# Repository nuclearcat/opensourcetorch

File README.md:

Opensource programmable... torch? light? flashlight? I dont know, but it is funny and i like it.

We have onboard:
3xRGB(parallel) light, indicator light, accelerometer, illumination sensor, USB-Serial (CH340) for debug, lithium battery charger.

Example applications: coming soon

Read ERRATA first, if you want to make your own!

ERRATA in v1.0   
* 32Khz oscillator on MCU not starting reliably. (Might be software issue.)

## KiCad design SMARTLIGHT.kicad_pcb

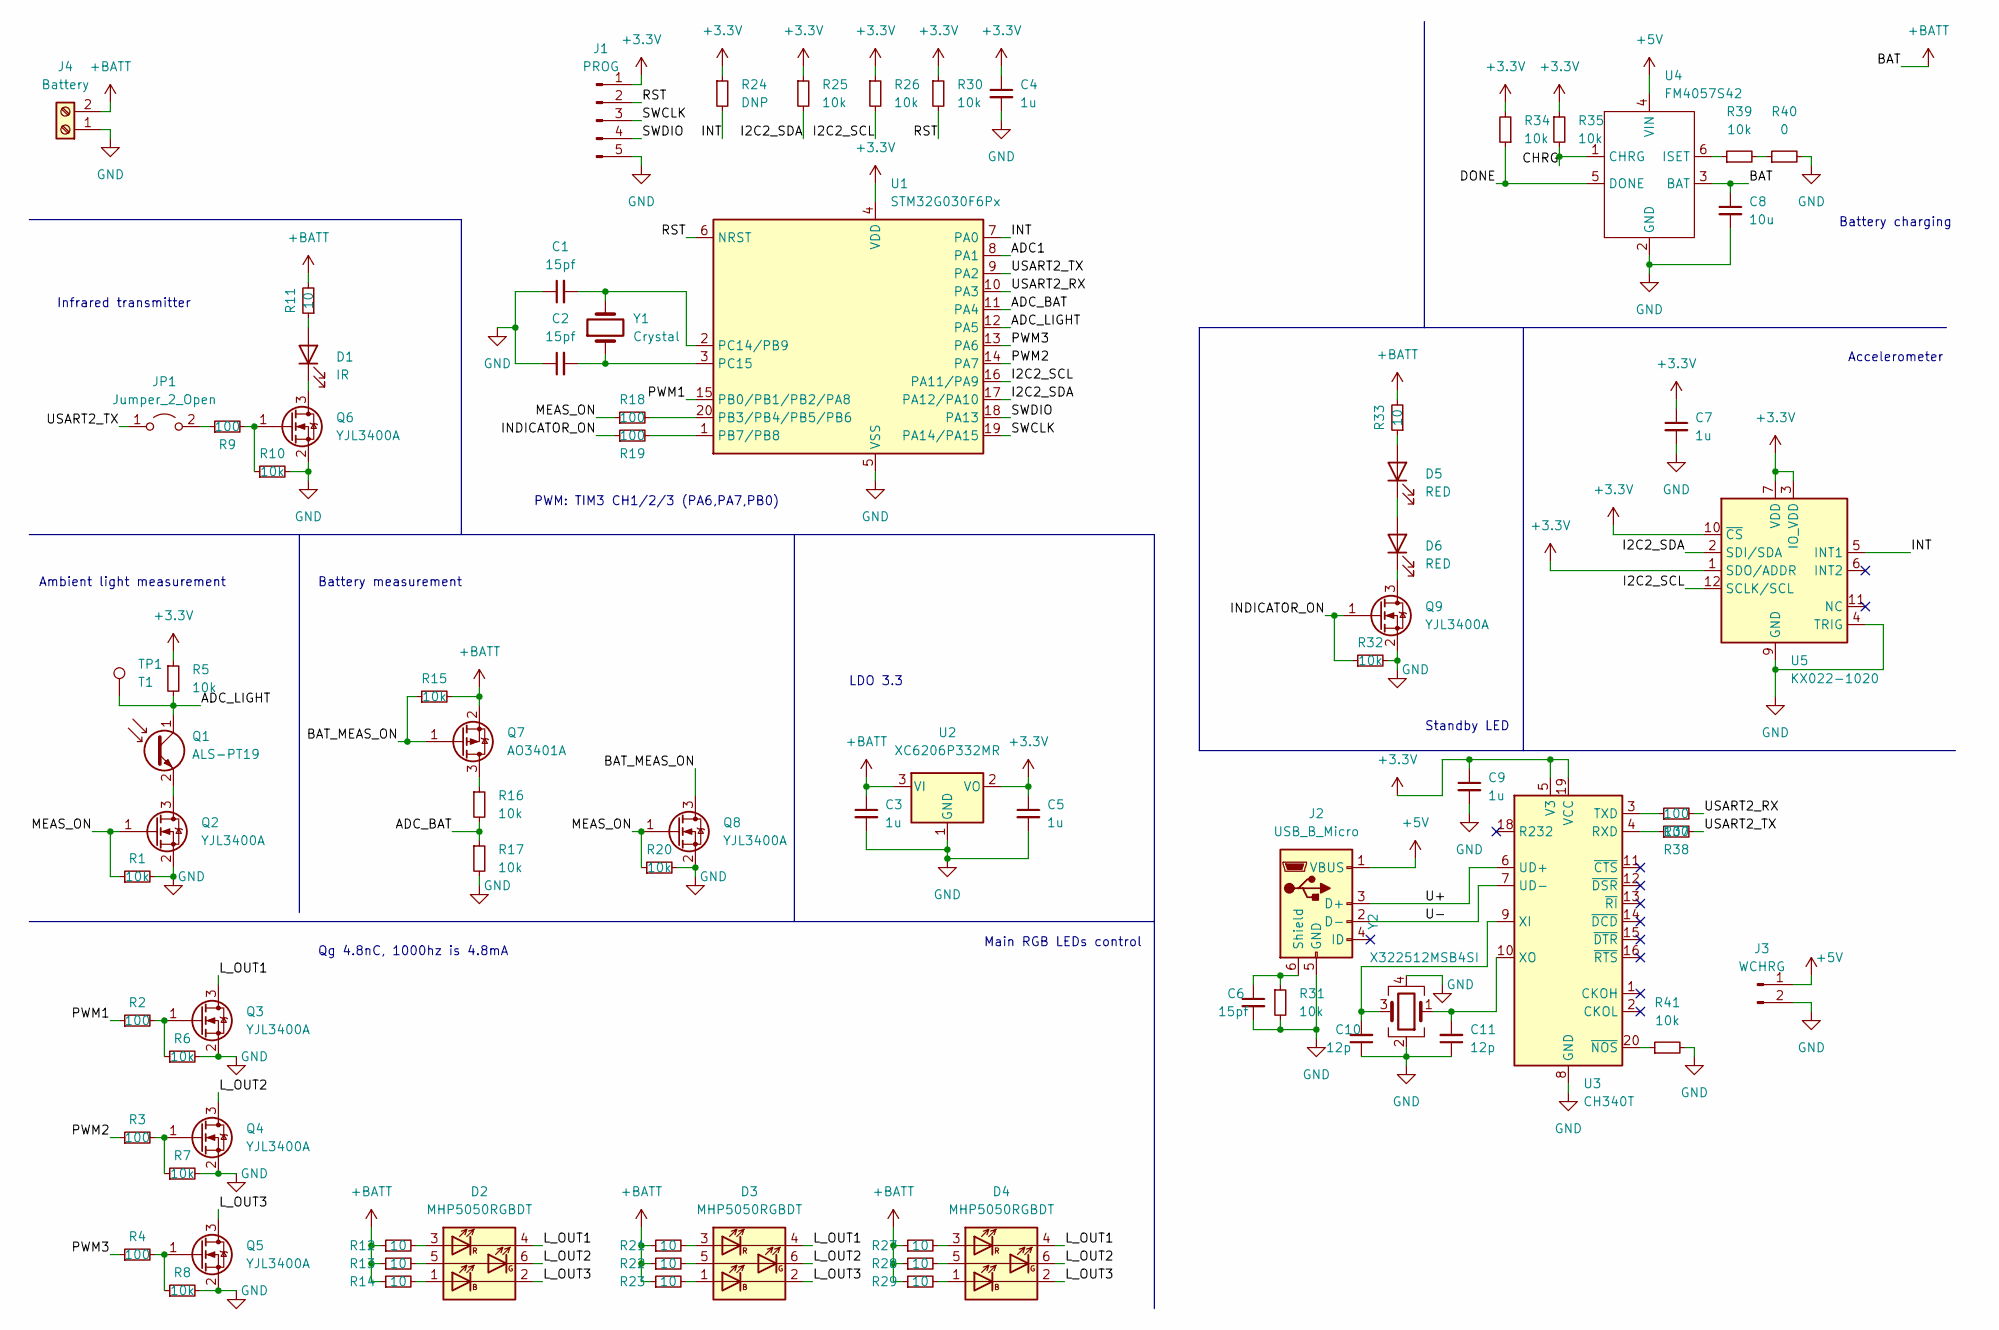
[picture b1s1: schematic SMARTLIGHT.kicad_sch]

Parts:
C1, C2, C6: 15pf; C_0603_1608Metric; LCSC PN C1644
C3, C4, C5, C7, C9: 1u; C_0603_1608Metric; LCSC PN C15849
C8: 10u; C_0603_1608Metric; LCSC PN C19702
C10, C11: 12p; C_0603_1608Metric; LCSC PN C38523
D1: IR; PinHeader_1x02_P2.54mm_Vertical
D2, D3, D4: MHP5050RGBDT; LCSC PN C409780
D5, D6: RED; LED_0805_2012Metric; LCSC PN C138549
J1: PROG; PinHeader_1x05_P2.54mm_Vertical
J2: USB_B_Micro; USB_Micro-B_Amphenol_10118194_Horizontal; LCSC PN C132563
J3: WCHRG; PinHeader_1x02_P2.54mm_Vertical
J4: Battery; PinHeader_1x02_P2.54mm_Vertical
JP1: Jumper_2_Open; PinHeader_1x02_P2.54mm_Vertical
Q1: ALS-PT19; LCSC PN C146233
Q2, Q3, Q4, Q5, Q6, Q8, Q9: YJL3400A; SOT-23; LCSC PN C699302
Q7: AO3401A; SOT-23; LCSC PN C15127
R1, R5, R6, R7, R8, R10, R15, R16, R17, R20, R25, R26, R30, R31, R32, R34, R35, R39, R41: 10k; R_0603_1608Metric; LCSC PN C25804
R2, R3, R4, R9, R18, R19, R37, R38: 100; R_0603_1608Metric; LCSC PN C22775
R11, R12, R13, R14, R21, R22, R23, R27, R28, R29, R33: 10; R_0603_1608Metric; LCSC PN C22859
R24: DNP; R_0603_1608Metric
R40: 0; R_0603_1608Metric; LCSC PN C21189
TP1: T1; TestPoint_Keystone_5000-5004_Miniature
U1: STM32G030F6Px; TSSOP-20_4.4x6.5mm_P0.65mm; LCSC PN C529330
U2: XC6206P332MR; SOT-23; LCSC PN C5446
U3: CH340T; SSOP-20_5.3x7.2mm_P0.65mm; LCSC PN C8689
U4: FM4057S42; SOT-23-6; LCSC PN C841287
U5: KX022-1020; LGA-12_2x2mm_P0.5mm; LCSC PN C694095
Y1: Crystal; Crystal_SMD_3215-2Pin_3.2x1.5mm; LCSC PN C32346
Y2: X322512MSB4SI; Oscillator_SMD_SeikoEpson_SG8002CE-4Pin_3.2x2.5mm; LCSC PN C9002

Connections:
+3V3: C4.1, C5.1, C7.1, C9.1, J1.1, R5.1, R24.1, R25.1, R26.1, R30.1, R34.2, R35.1, U1.4 (VDD), U2.2 (VO), U3.5 (V3), U3.19 (VCC), U5.1 (SDO/ADDR), U5.3 (IO_VDD), U5.7 (VDD), U5.10 (~CS)
+5V: J2.1 (VBUS), J3.1, U4.4 (VIN)
+BATT: C3.1, C8.1, J4.2, Q7.2 (S), R11.2, R12.1, R13.1, R14.1, R15.2, R21.1, R22.1, R23.1, R27.1, R28.1, R29.1, R33.2, U2.3 (VI), U4.3 (BAT)
/ADC1: U1.8 (PA1)
/ADC_BAT: R16.2, R17.1, U1.11 (PA4)
/ADC_LIGHT: Q1.1 (C), R5.2, TP1.1, U1.12 (PA5)
/BAT_MEAS_ON: Q7.1 (G), Q8.3 (D), R15.1
/CHRG: R35.2, U4.1 (CHRG)
/DONE: R34.1, U4.5 (DONE)
/I2C2_SCL: R26.2, U1.16 (PA11/PA9), U5.12 (SCLK/SCL)
/I2C2_SDA: R25.2, U1.17 (PA12/PA10), U5.2 (SDI/SDA)
/INDICATOR_ON: Q9.1 (G), R19.1, R32.1
/INT: R24.2, U1.7 (PA0), U5.5 (INT1)
/L_OUT1: D2.4 (KR), D3.4 (KR), D4.4 (KR), Q3.3 (D)
/L_OUT2: D2.6 (KR), D3.6 (KR), D4.6 (KR), Q4.3 (D)
/L_OUT3: D2.2 (KB), D3.2 (KB), D4.2 (KB), Q5.3 (D)
/MEAS_ON: Q2.1 (G), Q8.1 (G), R1.1, R18.1, R20.1
/PWM1: R2.1, U1.15 (PB0/PB1/PB2/PA8)
/PWM2: R3.1, U1.14 (PA7)
/PWM3: R4.1, U1.13 (PA6)
/RST: J1.2, R30.2, U1.6 (NRST)
/SWCLK: J1.3, U1.19 (PA14/PA15)
/SWDIO: J1.4, U1.18 (PA13)
/U+: J2.3 (D+), U3.6 (UD+)
/U-: J2.2 (D-), U3.7 (UD-)
/USART2_RX: R37.2, U1.10 (PA3)
/USART2_TX: JP1.1 (A), R38.2, U1.9 (PA2)
GND: C1.1, C2.1, C3.2, C4.2, C5.2, C6.2, C7.2, C8.2, C9.2, C10.1, C11.1, J1.5, J2.5 (GND), J3.2, J4.1, Q2.2 (S), Q3.2 (S), Q4.2 (S), Q5.2 (S), Q6.2 (S), Q8.2 (S), Q9.2 (S), R1.2, R6.2, R7.2, R8.2, R10.2, R17.2, R20.2, R31.2, R32.2, R40.2, R41.2, U1.5 (VSS), U2.1 (GND), U3.8 (GND), U4.2 (GND), U5.4 (TRIG), U5.8 (GND), U5.9 (GND), Y2.2, Y2.4
unnamed: C1.2, U1.2 (PC14/PB9), Y1.2
unnamed: C2.2, U1.3 (PC15), Y1.1
unnamed: C6.1, J2.6 (Shield), R31.1
unnamed: C10.2, U3.9 (XI), Y2.3
unnamed: C11.2, U3.10 (XO), Y2.1
unnamed: D1.1 (K), Q6.3 (D)
unnamed: D1.2 (A), R11.1
unnamed: D2.1 (AB), R14.2
unnamed: D2.3 (AR), R12.2
unnamed: D2.5 (AG), R13.2
unnamed: D3.1 (AB), R23.2
unnamed: D3.3 (AR), R21.2
unnamed: D3.5 (AG), R22.2
unnamed: D4.1 (AB), R29.2
unnamed: D4.3 (AR), R27.2
unnamed: D4.5 (AG), R28.2
unnamed: D5.1 (K), D6.2 (A)
unnamed: D5.2 (A), R33.1
unnamed: D6.1 (K), Q9.3 (D)
unnamed: JP1.2 (B), R9.1
unnamed: Q1.2 (E), Q2.3 (D)
unnamed: Q3.1 (G), R2.2, R6.1
unnamed: Q4.1 (G), R3.2, R7.1
unnamed: Q5.1 (G), R4.2, R8.1
unnamed: Q6.1 (G), R9.2, R10.1
unnamed: Q7.3 (D), R16.1
unnamed: R18.2, U1.20 (PB3/PB4/PB5/PB6)
unnamed: R19.2, U1.1 (PB7/PB8)
unnamed: R37.1, U3.3 (TXD)
unnamed: R38.1, U3.4 (RXD)
unnamed: R39.1, U4.6 (ISET)
unnamed: R39.2, R40.1
unnamed: R41.1, U3.20 (~NOS)

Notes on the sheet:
Ambient light measurement
Infrared transmitter
Accelerometer
Standby LED
PWM: TIM3 CH1/2/3 (PA6,PA7,PB0)
Battery measurement
Qg 4.8nC, 1000hz is 4.8mA
Battery charging
Main RGB LEDs control
LDO 3.3

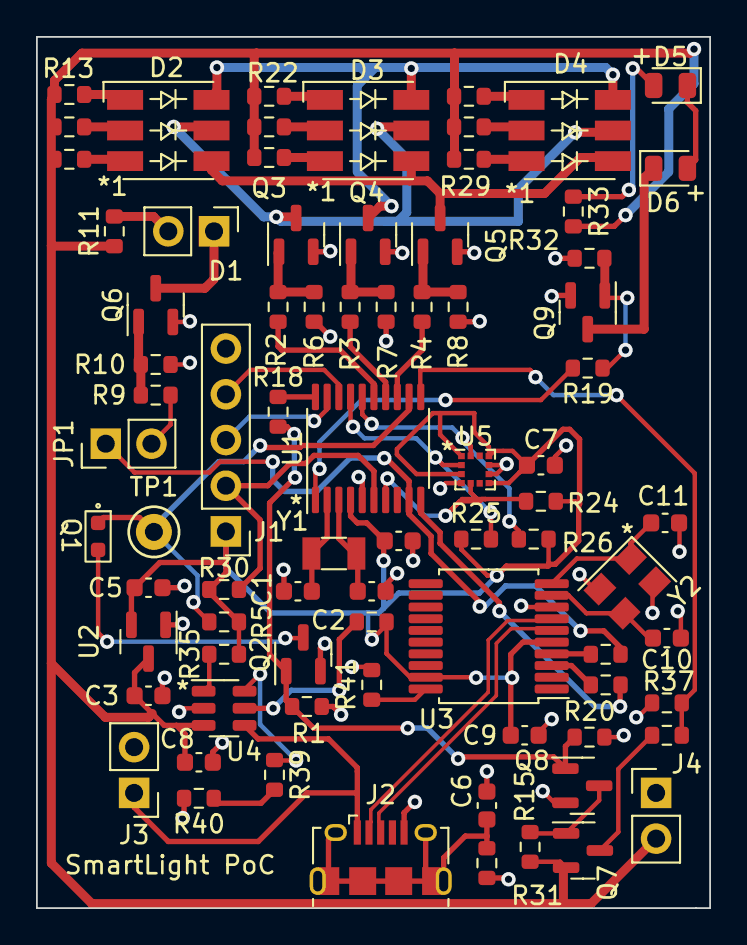
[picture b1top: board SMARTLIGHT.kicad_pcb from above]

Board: 2 copper layers, 37.4 x 48.4 mm, 79 parts (0 on the bottom side), 60 nets.

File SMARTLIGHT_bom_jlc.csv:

"Comment","Designator","Footprint","LCSC Part #"
"15pf","C1,C2,C6","C_0603_1608Metric","C1644"
"1u","C3,C4,C5,C7,C9","C_0603_1608Metric","C15849"
"10u","C8","C_0603_1608Metric","C19702"
"12p","C10,C11","C_0603_1608Metric","C38523"
"MHP5050RGBDT","D2,D3,D4","MHP5050RGBDT","C409780"
"RED","D5,D6","LED_0805_2012Metric","C138549"
"USB_B_Micro","J2","USB_Micro-B_Amphenol_10118194_Horizontal","C132563"
"ALS-PT19","Q1","ALS-PT19","C146233"
"YJL3400A","Q2,Q3,Q4,Q5,Q6,Q8,Q9","SOT-23","C699302"
"AO3401A","Q7","SOT-23","C15127"
"10k","R1,R5,R6,R7,R8,R10,R15,R16,R17,R20,R25,R26,R30,R31,R32,R34,R35,R39,R41","R_0603_1608Metric","C25804"
"100","R2,R3,R4,R9,R18,R19,R37,R38","R_0603_1608Metric","C22775"
"10","R11,R12,R13,R14,R21,R22,R23,R27,R28,R29,R33","R_0603_1608Metric","C22859"
"0","R40","R_0603_1608Metric","C21189"
"STM32G030F6Px","U1","TSSOP-20_4.4x6.5mm_P0.65mm","C529330"
"XC6206P332MR","U2","SOT-23","C5446"
"CH340T","U3","SSOP-20_5.3x7.2mm_P0.65mm","C8689"
"FM4057S42","U4","SOT-23-6","C841287"
"KX022-1020","U5","LGA-12_2x2mm_P0.5mm","C694095"
"Crystal","Y1","Crystal_SMD_3215-2Pin_3.2x1.5mm","C32346"
"X322512MSB4SI","Y2","Oscillator_SMD_SeikoEpson_SG8002CE-4Pin_3.2x2.5mm","C9002"

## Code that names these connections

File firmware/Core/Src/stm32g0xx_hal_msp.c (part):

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    __HAL_RCC_GPIOA_CLK_ENABLE();
    /**ADC1 GPIO Configuration
    PA1     ------> ADC1_IN1
    PA4     ------> ADC1_IN4
    PA5     ------> ADC1_IN5
    */
    GPIO_InitStruct.Pin = GPIO_PIN_1|GPIO_PIN_4|GPIO_PIN_5;
    GPIO_InitStruct.Mode = GPIO_MODE_ANALOG;
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
    /**ADC1 GPIO Configuration
    PA1     ------> ADC1_IN1
    PA4     ------> ADC1_IN4
    PA5     ------> ADC1_IN5
    */
    HAL_GPIO_DeInit(GPIOA, GPIO_PIN_1|GPIO_PIN_4|GPIO_PIN_5);

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
    __HAL_RCC_GPIOA_CLK_ENABLE();
    /**I2C2 GPIO Configuration
    PA11 [PA9]     ------> I2C2_SCL
    PA12 [PA10]     ------> I2C2_SDA
    */
    GPIO_InitStruct.Pin = GPIO_PIN_11|GPIO_PIN_12;
    GPIO_InitStruct.Mode = GPIO_MODE_AF_OD;
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    __HAL_RCC_I2C2_CLK_DISABLE();

    /**I2C2 GPIO Configuration
    PA11 [PA9]     ------> I2C2_SCL
    PA12 [PA10]     ------> I2C2_SDA
    */
    HAL_GPIO_DeInit(GPIOA, GPIO_PIN_11);

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    __HAL_RCC_GPIOA_CLK_ENABLE();
    __HAL_RCC_GPIOB_CLK_ENABLE();
    /**TIM3 GPIO Configuration
    PA6     ------> TIM3_CH1
    PA7     ------> TIM3_CH2
    PB0     ------> TIM3_CH3
    */
    GPIO_InitStruct.Pin = GPIO_PIN_6|GPIO_PIN_7;
    GPIO_InitStruct.Mode = GPIO_MODE_AF_PP;
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
    __HAL_RCC_GPIOA_CLK_ENABLE();
    /**USART2 GPIO Configuration
    PA2     ------> USART2_TX
    PA3     ------> USART2_RX
    */
    GPIO_InitStruct.Pin = GPIO_PIN_2|GPIO_PIN_3;
    GPIO_InitStruct.Mode = GPIO_MODE_AF_PP;
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    __HAL_RCC_USART2_CLK_DISABLE();

    /**USART2 GPIO Configuration
    PA2     ------> USART2_TX
    PA3     ------> USART2_RX
    */
    HAL_GPIO_DeInit(GPIOA, GPIO_PIN_2|GPIO_PIN_3);

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
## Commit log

2022-01-23 Add more information
2022-01-23 Create LICENSE
2022-01-23 Formatting
2022-01-23 Sample code to run
2022-01-23 Accelerometer check
2022-01-23 Working feature
2022-01-24 Add slow glow
2022-01-24 Convert dos2unix

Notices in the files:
firmware/Core/Src/stm32g0xx_hal_msp.c:
Copyright (c) 2022 STMicroelectronics.
All rights reserved.
This software is licensed under terms that can be found in the LICENSE file
